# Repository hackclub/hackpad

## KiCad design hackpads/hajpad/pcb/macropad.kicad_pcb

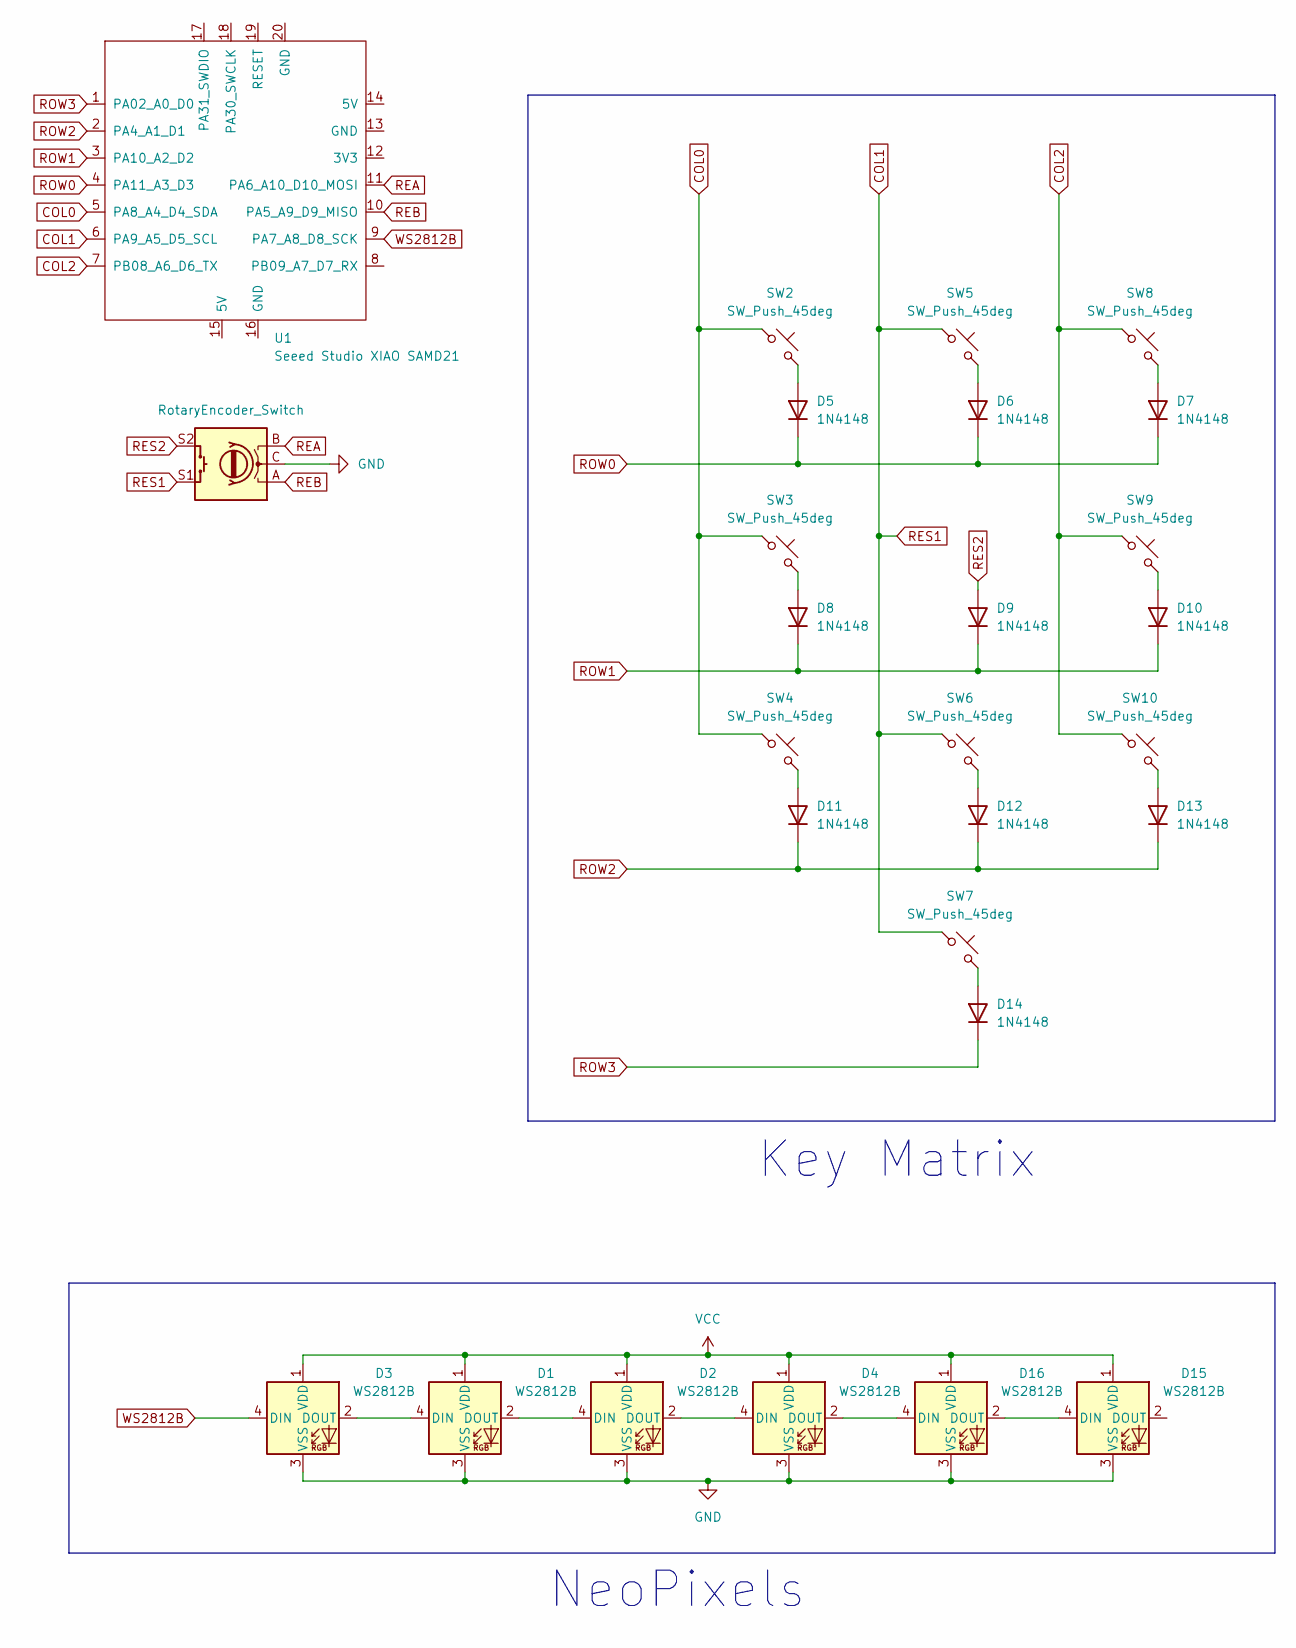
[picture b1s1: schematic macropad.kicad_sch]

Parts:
D1, D2, D3, D4, D15, D16: WS2812B; LED_WS2812B_PLCC4_5.0x5.0mm_P3.2mm
D5, D6, D7, D8, D9, D10, D11, D12, D13, D14: 1N4148; D_DO-35_SOD27_P7.62mm_Horizontal
SW1: RotaryEncoder_Switch; RotaryEncoder_Alps_EC11E-Switch_Vertical_H20mm_CircularMoun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
SW2, SW3, SW4, SW5, SW6, SW8, SW9, SW10: SW_Push_45deg; SW_Cherry_MX_PCB_1.00u
SW7: SW_Push_45deg; SW_Cherry_MX_PCB_3.00u_90deg
U1: Seeed Studio XIAO SAMD21; XIAO-Generic-Hybrid-14P-2.54-21X17.8MM0-alternate

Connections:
COL0: SW2.1, SW3.1, SW4.1, U1.5 (PA8_A4_D4_SDA)
COL1: SW1.S1, SW5.1, SW6.1, SW7.1, U1.6 (PA9_A5_D5_SCL)
COL2: SW8.1, SW9.1, SW10.1, U1.7 (PB08_A6_D6_TX)
GND: D1.3 (VSS), D2.3 (VSS), D3.3 (VSS), D4.3 (VSS), D15.3 (VSS), D16.3 (VSS), SW1.C
unnamed: D1.4 (DIN), D3.2 (DOUT)
unnamed: D1.2 (DOUT), D2.4 (DIN)
unnamed: D2.2 (DOUT), D4.4 (DIN)
unnamed: D5.2 (A), SW2.2
unnamed: D6.2 (A), SW5.2
unnamed: D7.2 (A), SW8.2
unnamed: D8.2 (A), SW3.2
unnamed: D10.2 (A), SW9.2
unnamed: D11.2 (A), SW4.2
unnamed: D12.2 (A), SW6.2
unnamed: D13.2 (A), SW10.2
unnamed: D14.2 (A), SW7.2
unnamed: D15.4 (DIN), D16.2 (DOUT)
unnamed: D4.2 (DOUT), D16.4 (DIN)
REA: SW1.B, U1.11 (PA6_A10_D10_MOSI)
REB: SW1.A, U1.10 (PA5_A9_D9_MISO)
RES2: D9.2 (A), SW1.S2
ROW0: D5.1 (K), D6.1 (K), D7.1 (K), U1.4 (PA11_A3_D3)
ROW1: D8.1 (K), D9.1 (K), D10.1 (K), U1.3 (PA10_A2_D2)
ROW2: D11.1 (K), D12.1 (K), D13.1 (K), U1.2 (PA4_A1_D1)
ROW3: D14.1 (K), U1.1 (PA02_A0_D0)
VCC: D1.1 (VDD), D2.1 (VDD), D3.1 (VDD), D4.1 (VDD), D15.1 (VDD), D16.1 (VDD)
WS2812B: D3.4 (DIN), U1.9 (PA7_A8_D8_SCK)

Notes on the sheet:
NeoPixels
Key Matrix

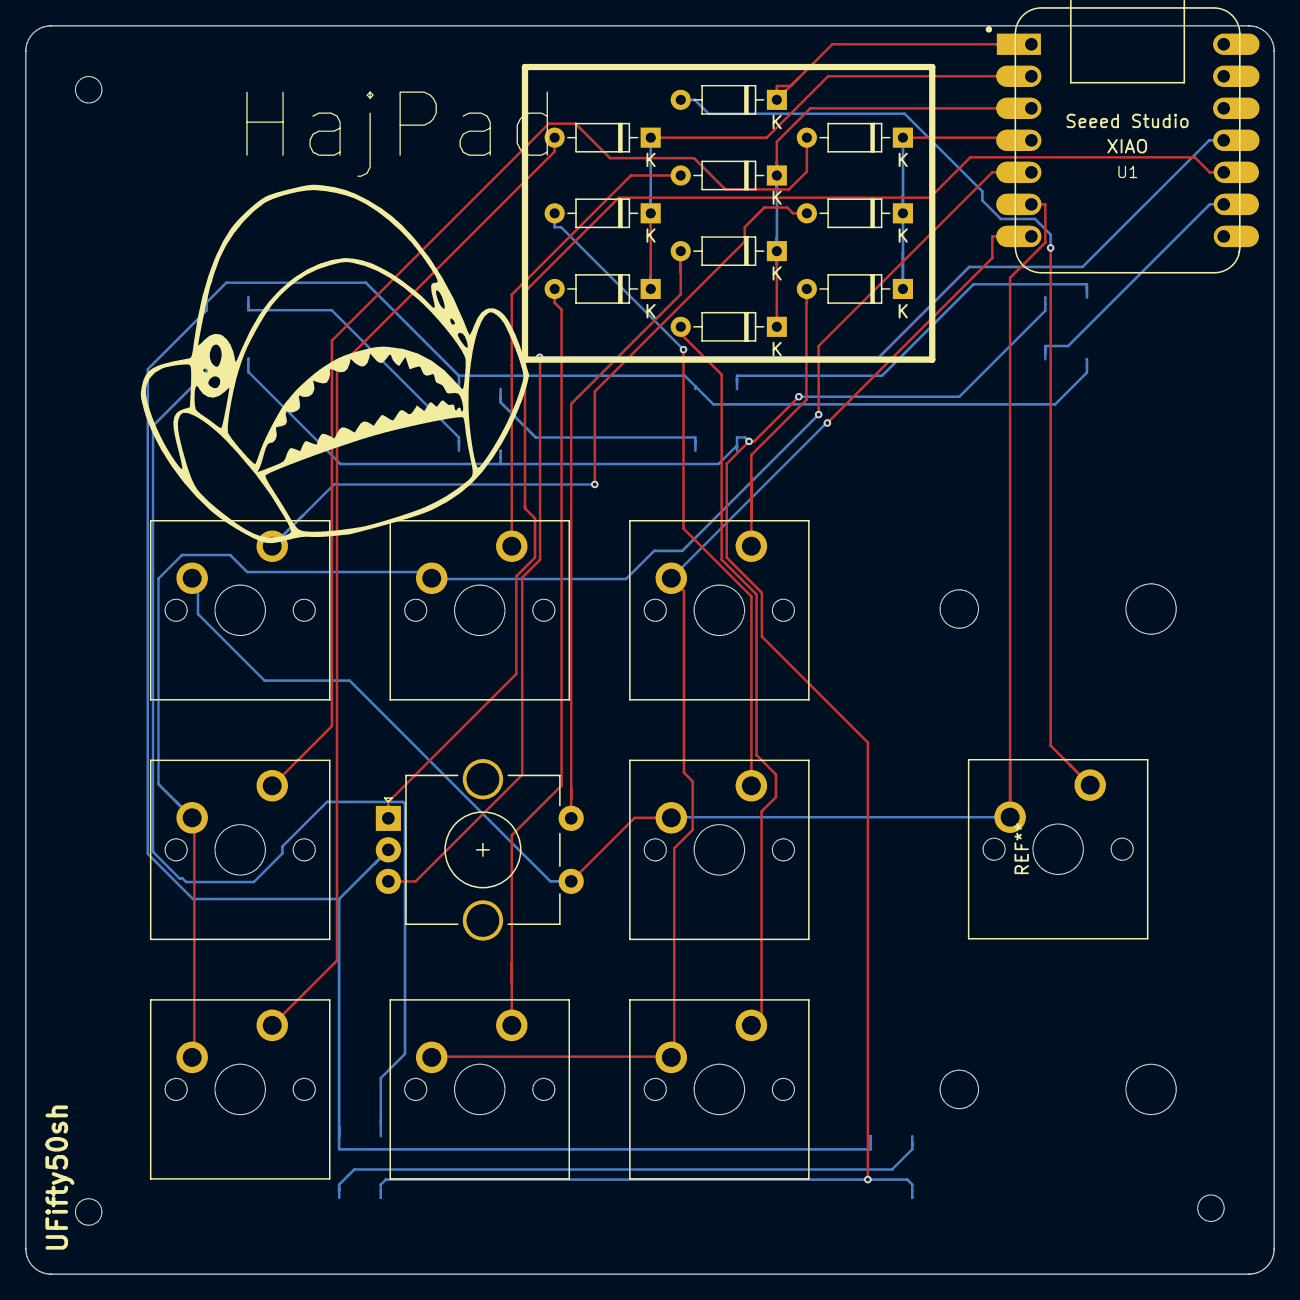
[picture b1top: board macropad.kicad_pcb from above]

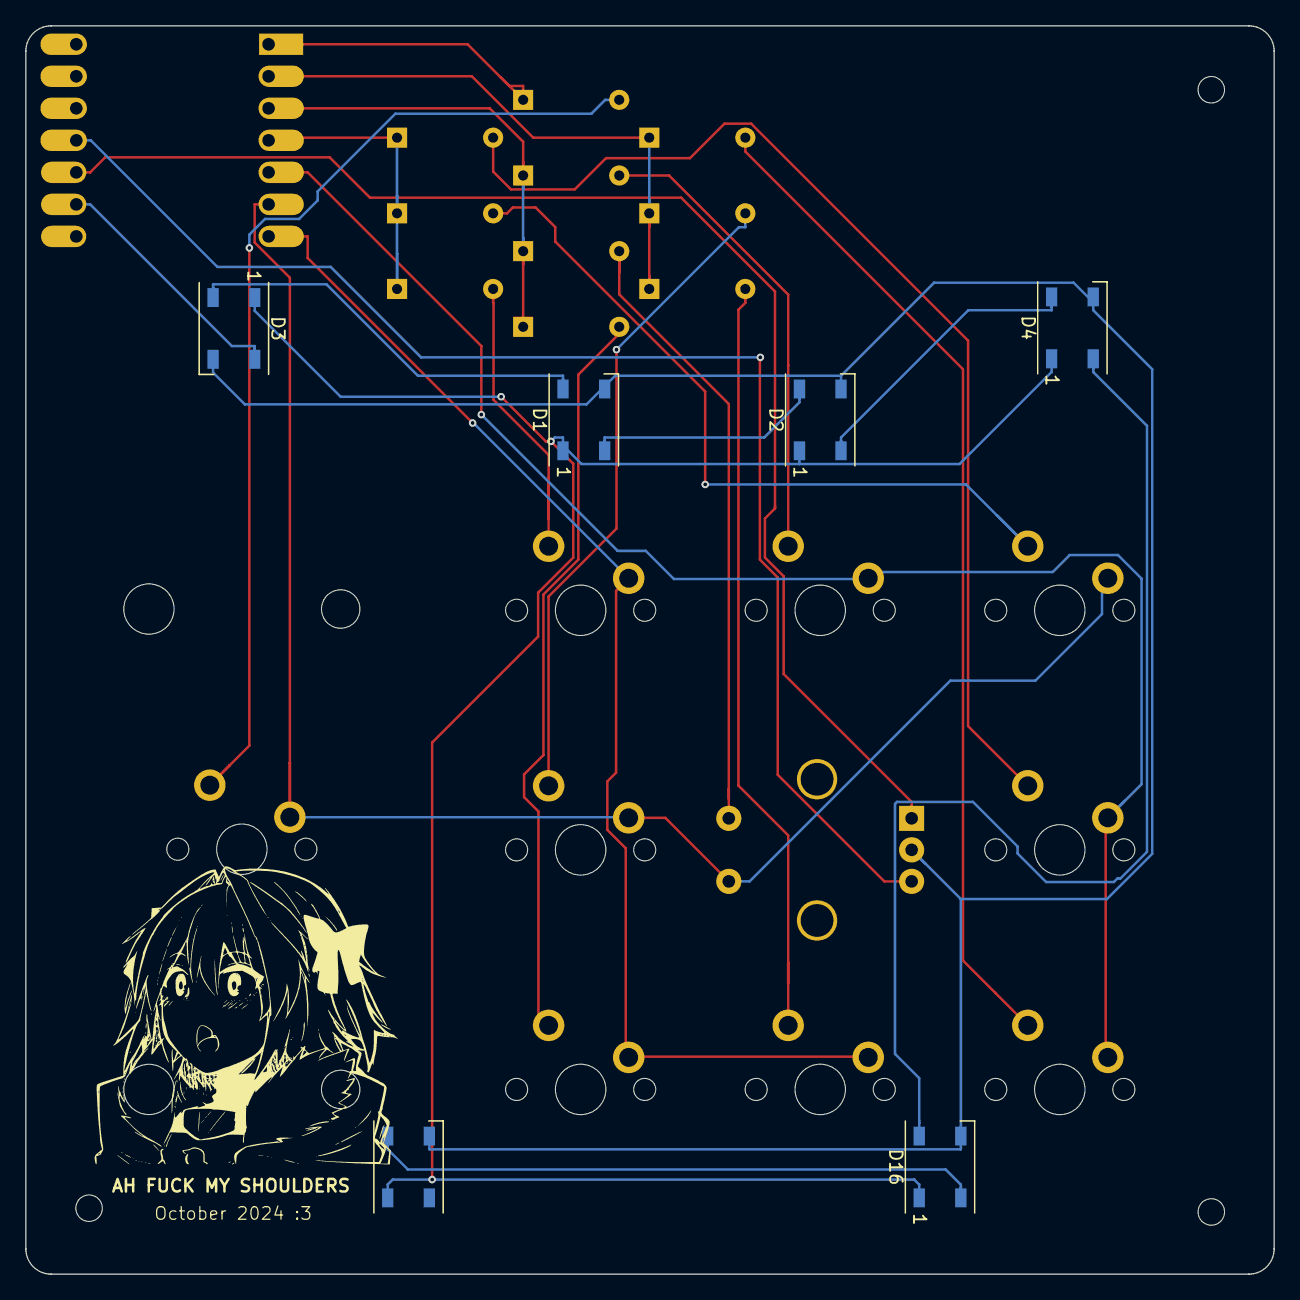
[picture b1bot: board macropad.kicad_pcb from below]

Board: 2 copper layers, 99.0 x 99.0 mm, 27 parts (6 on the bottom side), 27 nets.

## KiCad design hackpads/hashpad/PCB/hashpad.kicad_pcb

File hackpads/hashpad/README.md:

# Hash-AK's Hackpad (HashPad)

This is my macropad, made for the (awesome!) Hackpad V2 program of Hackclub (https://hackpad.hackclub.com)

I will use this hackpad for (eventually) Hyprland control (like workspace switching) or as a mini protable keyboard (TBD)

What I found particuliary difficult was the case design, I couldn't use Fusion and FreeCAD was hard to use, even with the tutorial (Cyao in the slack helped me alot for that).

# Features

- OLED Display
- Reverse-mounted LEDs to make a full backlighting
- Rotary Encoder to control some stuff
- Matrix with diodes to prevent ghosting

BOM :

- 1x trought-hole SEEED XIAO RP2040
- 9x MX-Style switches (preferably transluent one)
- 9x SK8612-e MINI led (for reverse mounting)
- 1x Rotary Encoder EC11
- 1x SD1306 0.96" OLED display
- 9x Through-hole 1N4148 Diodes
- 4x M3x16mm screws
- 4x M3 hex nuts

# Images

_Scheatics of the macropad_

_PCB of the macropad_

_Front of the board (3D Model)_

_Back of the board (3D Model, the SK8612 is missing in the images, there's only a cutout/pads)_

_Full image of the case with the PCB._

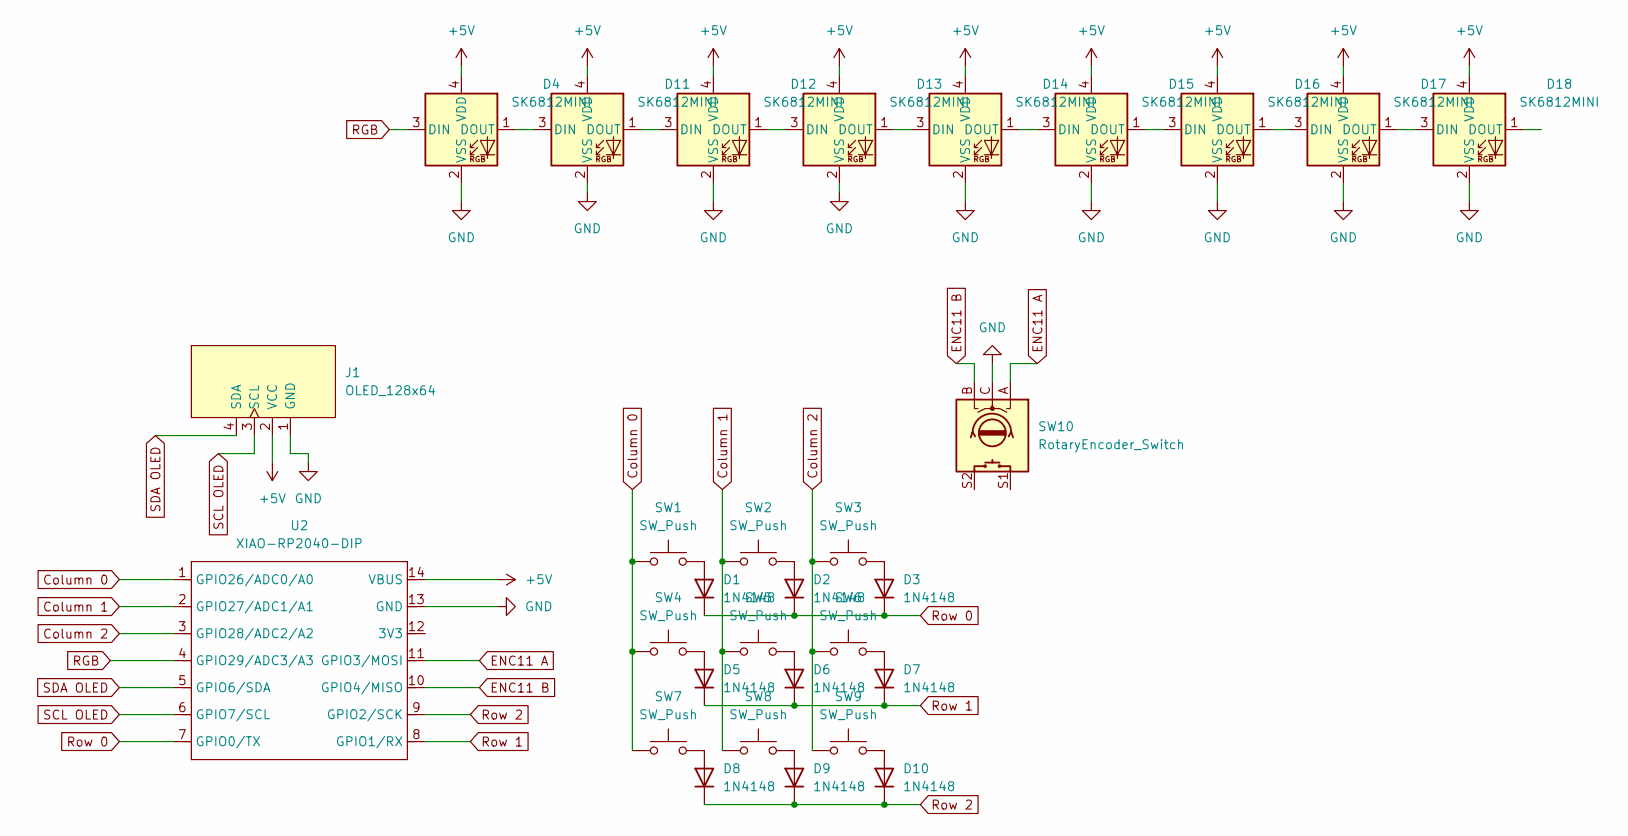
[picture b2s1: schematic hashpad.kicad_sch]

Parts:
D1, D2, D3, D5, D6, D7, D8, D9, D10: 1N4148; D_DO-35_SOD27_P7.62mm_Horizontal
D4, D11, D12, D13, D14, D15, D16, D17, D18: SK6812MINI; SK6812MINI-E
J1: OLED_128x64
SW1, SW2, SW3, SW4, SW5, SW6, SW7, SW8, SW9: SW_Push; MX_PCB_1.00u
SW10: RotaryEncoder_Switch; Encoder_EC11_MX
U2: XIAO-RP2040-DIP; Seeed_XIAO_RP2040

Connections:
+5V: D4.4 (VDD), D11.4 (VDD), D12.4 (VDD), D13.4 (VDD), D14.4 (VDD), D15.4 (VDD), D16.4 (VDD), D17.4 (VDD), D18.4 (VDD), J1.2 (VCC), U2.14 (VBUS)
Column 0: SW1.1, SW4.1, SW7.1, U2.1 (GPIO26/ADC0/A0)
Column 1: SW2.1, SW5.1, SW8.1, U2.2 (GPIO27/ADC1/A1)
Column 2: SW3.1, SW6.1, SW9.1, U2.3 (GPIO28/ADC2/A2)
ENC11 A: SW10.A, U2.11 (GPIO3/MOSI)
ENC11 B: SW10.B, U2.10 (GPIO4/MISO)
GND: D4.2 (VSS), D11.2 (VSS), D12.2 (VSS), D13.2 (VSS), D14.2 (VSS), D15.2 (VSS), D16.2 (VSS), D17.2 (VSS), D18.2 (VSS), J1.1 (GND), SW10.C, U2.13 (GND)
unnamed: D1.2 (A), SW1.2
unnamed: D2.2 (A), SW2.2
unnamed: D3.2 (A), SW3.2
unnamed: D5.2 (A), SW4.2
unnamed: D6.2 (A), SW5.2
unnamed: D7.2 (A), SW6.2
unnamed: D8.2 (A), SW7.2
unnamed: D9.2 (A), SW8.2
unnamed: D10.2 (A), SW9.2
unnamed: D4.1 (DOUT), D11.3 (DIN)
unnamed: D11.1 (DOUT), D12.3 (DIN)
unnamed: D12.1 (DOUT), D13.3 (DIN)
unnamed: D13.1 (DOUT), D14.3 (DIN)
unnamed: D14.1 (DOUT), D15.3 (DIN)
unnamed: D15.1 (DOUT), D16.3 (DIN)
unnamed: D16.1 (DOUT), D17.3 (DIN)
unnamed: D17.1 (DOUT), D18.3 (DIN)
RGB: D4.3 (DIN), U2.4 (GPIO29/ADC3/A3)
Row 0: D1.1 (K), D2.1 (K), D3.1 (K), U2.7 (GPIO0/TX)
Row 1: D5.1 (K), D6.1 (K), D7.1 (K), U2.8 (GPIO1/RX)
Row 2: D8.1 (K), D9.1 (K), D10.1 (K), U2.9 (GPIO2/SCK)
SCL OLED: J1.3 (SCL), U2.6 (GPIO7/SCL)
SDA OLED: J1.4 (SDA), U2.5 (GPIO6/SDA)

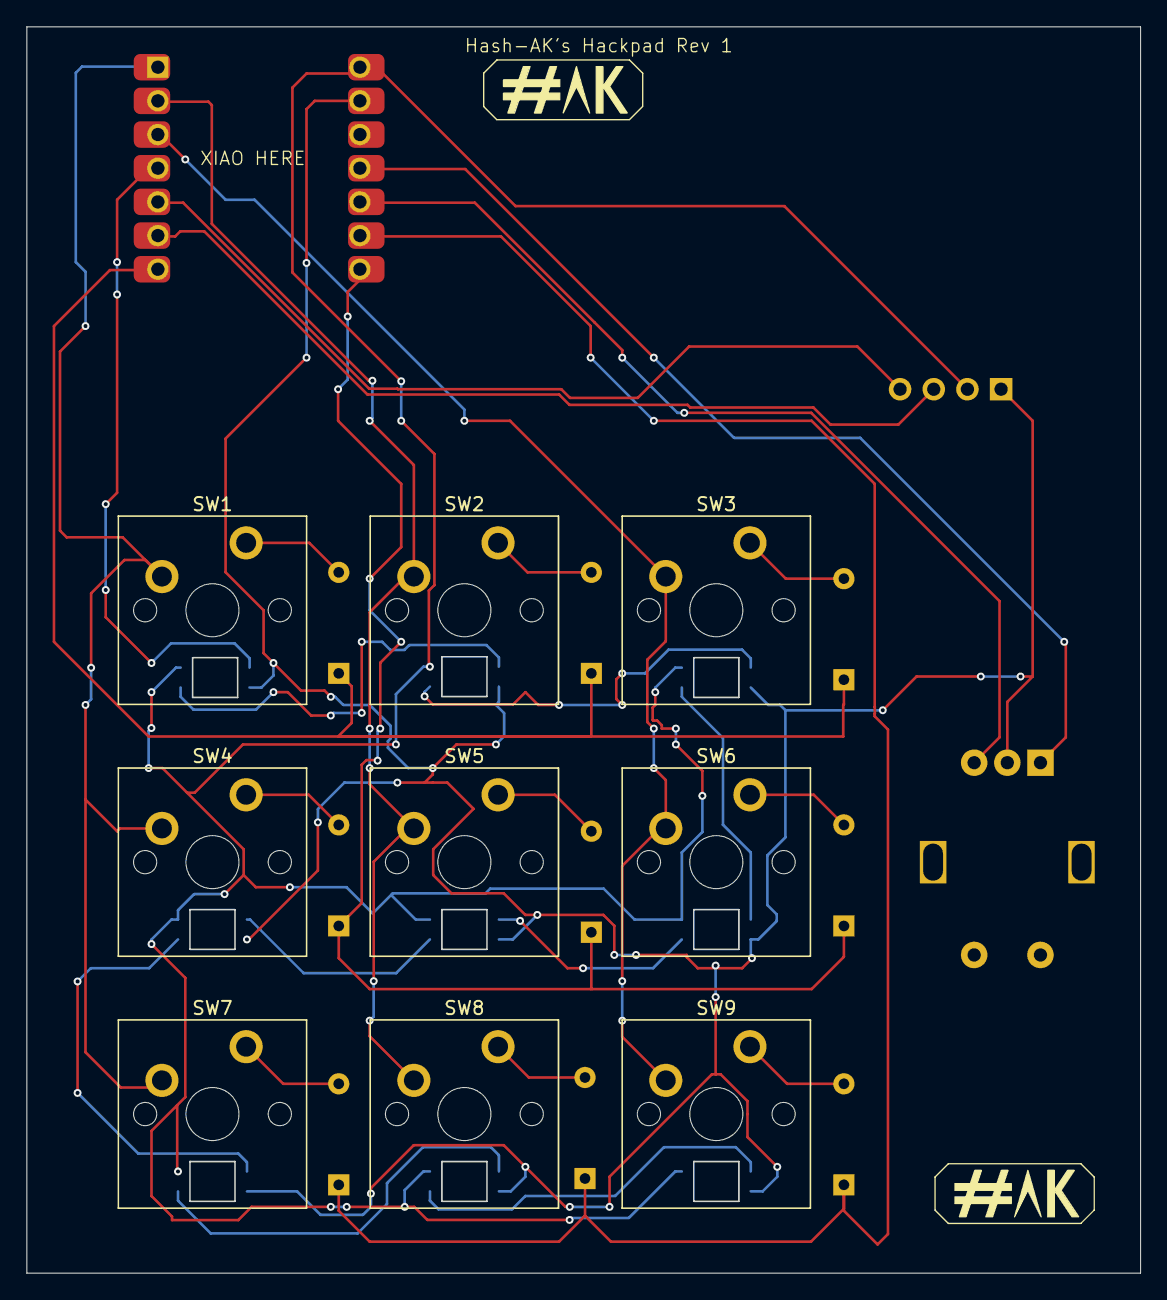
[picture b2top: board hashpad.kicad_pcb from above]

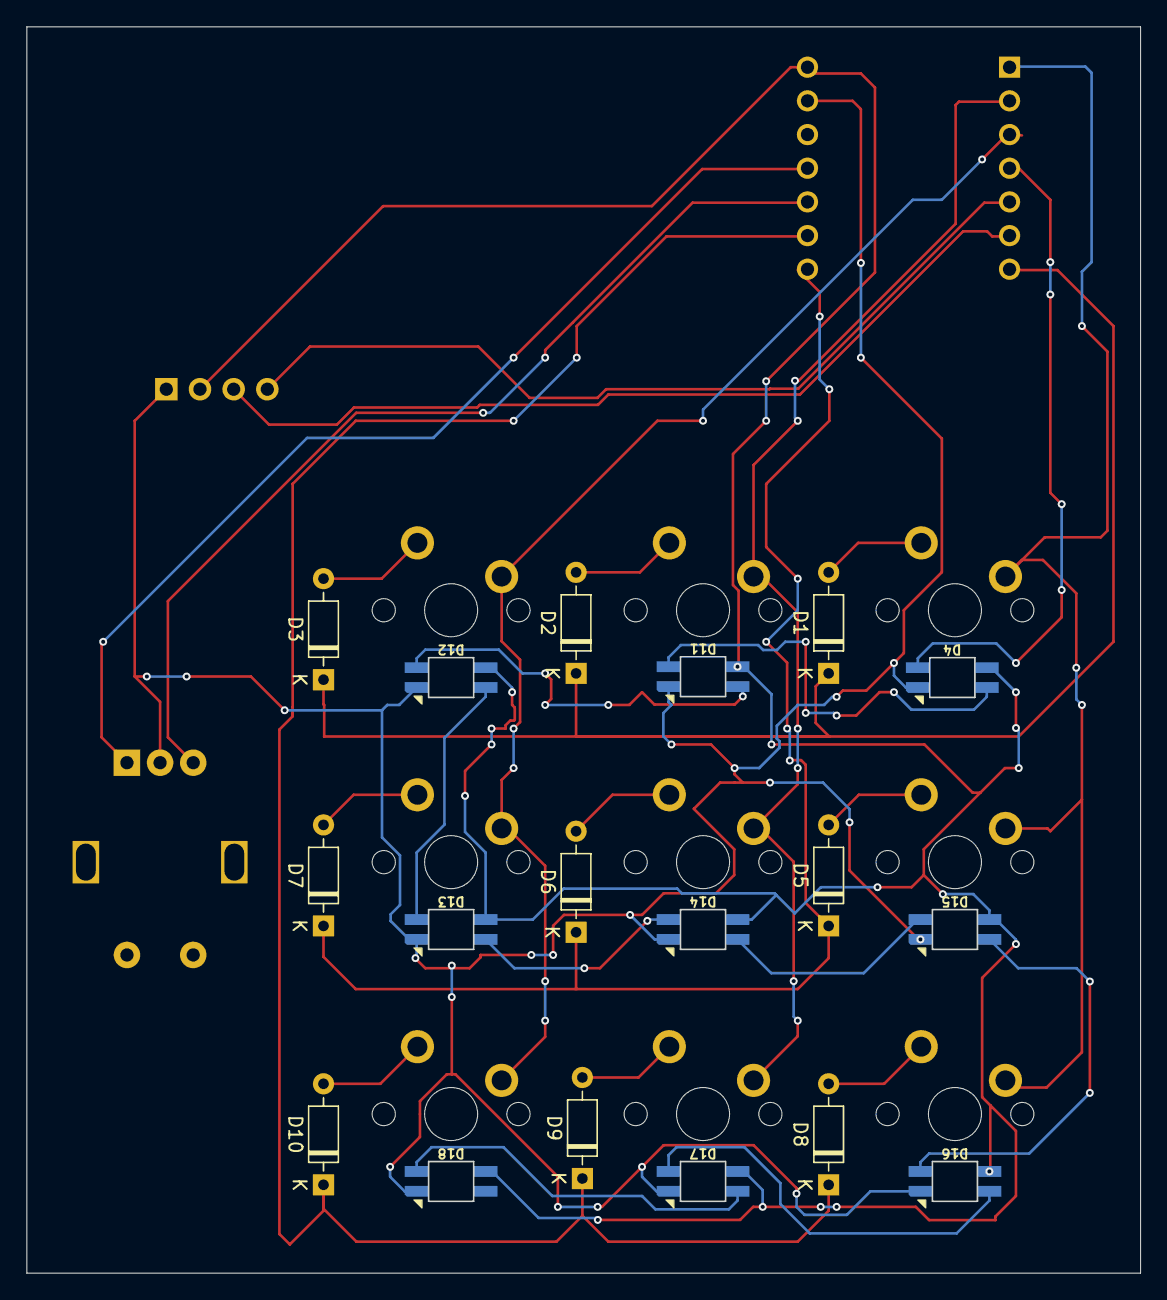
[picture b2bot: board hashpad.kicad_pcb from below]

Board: 2 copper layers, 84.0 x 94.0 mm, 30 parts (18 on the bottom side), 30 nets.

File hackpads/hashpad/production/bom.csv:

Designator,Footprint,Quantity,Value,LCSC Part #
"D1, D10, D2, D3, D5, D6, D7, D8, D9",D_DO-35_SOD27_P7.62mm_Horizontal,9,1N4148,
"D11, D12, D13, D14, D15, D16, D17, D18, D4",SK6812MINI-E,9,SK6812MINI,
J1,OLED_128x64,1,OLED_128x64,
"SW1, SW2, SW3, SW4, SW5, SW6, SW7, SW8, SW9",MX_PCB_1.00u,9,SW_Push,
SW10,Encoder_EC11_MX,1,RotaryEncoder_Switch,
U2,Seeed_XIAO_RP2040,1,XIAO-RP2040-DIP,

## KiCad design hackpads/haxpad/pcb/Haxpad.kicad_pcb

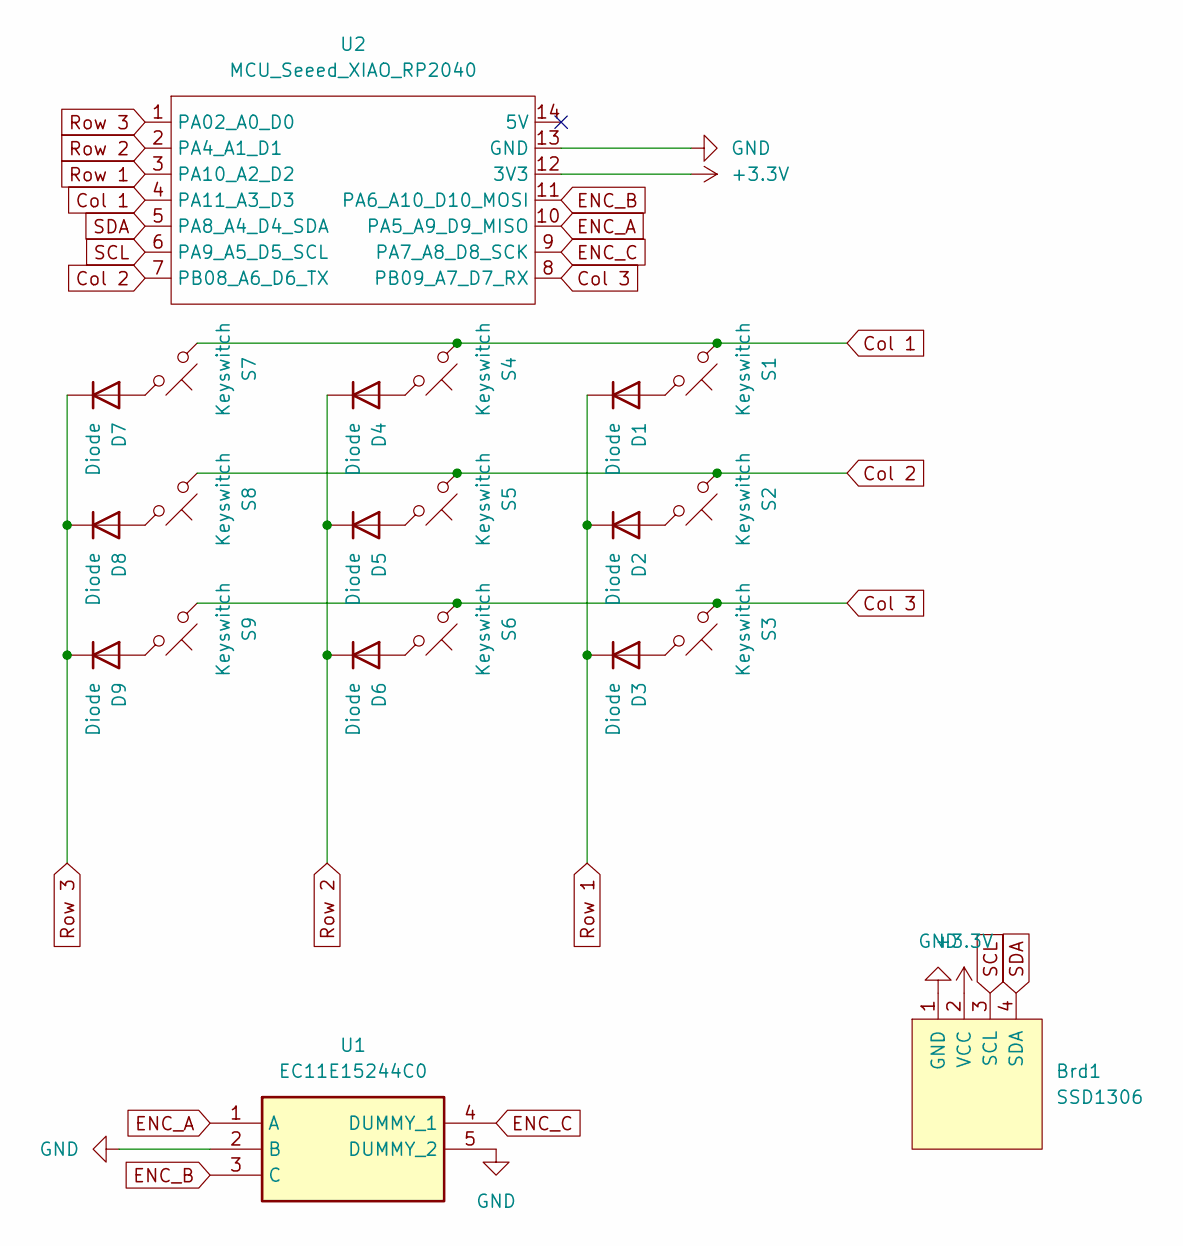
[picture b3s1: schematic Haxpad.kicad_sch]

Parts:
Brd1: SSD1306; 128x64OLED
D1, D2, D3, D4, D5, D6, D7, D8, D9: Diode; Diode_DO-35
S1, S2, S3, S4, S5, S6, S7, S8, S9: Keyswitch; MX-Hotswap-1U
U1: EC11E15244C0; EC11B202440M; Manufacturer_Part_Number EC11E15244C0
U2: MCU_Seeed_XIAO_RP2040; Seeed_XIAO_RP2040

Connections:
+3.3V: Brd1.2 (VCC), U2.12 (3V3)
Col 1: S1.1, S4.1, S7.1, U2.4 (PA11_A3_D3)
Col 2: S2.1, S5.1, S8.1, U2.7 (PB08_A6_D6_TX)
Col 3: S3.1, S6.1, S9.1, U2.8 (PB09_A7_D7_RX)
ENC_A: U1.1 (A), U2.10 (PA5_A9_D9_MISO)
ENC_B: U1.3 (C), U2.11 (PA6_A10_D10_MOSI)
ENC_C: U1.4 (DUMMY_1), U2.9 (PA7_A8_D8_SCK)
GND: Brd1.1 (GND), U1.2 (B), U1.5 (DUMMY_2), U2.13 (GND)
unnamed: D1.2 (A), S1.2
unnamed: D2.2 (A), S2.2
unnamed: D3.2 (A), S3.2
unnamed: D4.2 (A), S4.2
unnamed: D5.2 (A), S5.2
unnamed: D6.2 (A), S6.2
unnamed: D7.2 (A), S7.2
unnamed: D8.2 (A), S8.2
unnamed: D9.2 (A), S9.2
Row 1: D1.1 (K), D2.1 (K), D3.1 (K), U2.3 (PA10_A2_D2)
Row 2: D4.1 (K), D5.1 (K), D6.1 (K), U2.2 (PA4_A1_D1)
Row 3: D7.1 (K), D8.1 (K), D9.1 (K), U2.1 (PA02_A0_D0)
SCL: Brd1.3 (SCL), U2.6 (PA9_A5_D5_SCL)
SDA: Brd1.4 (SDA), U2.5 (PA8_A4_D4_SDA)

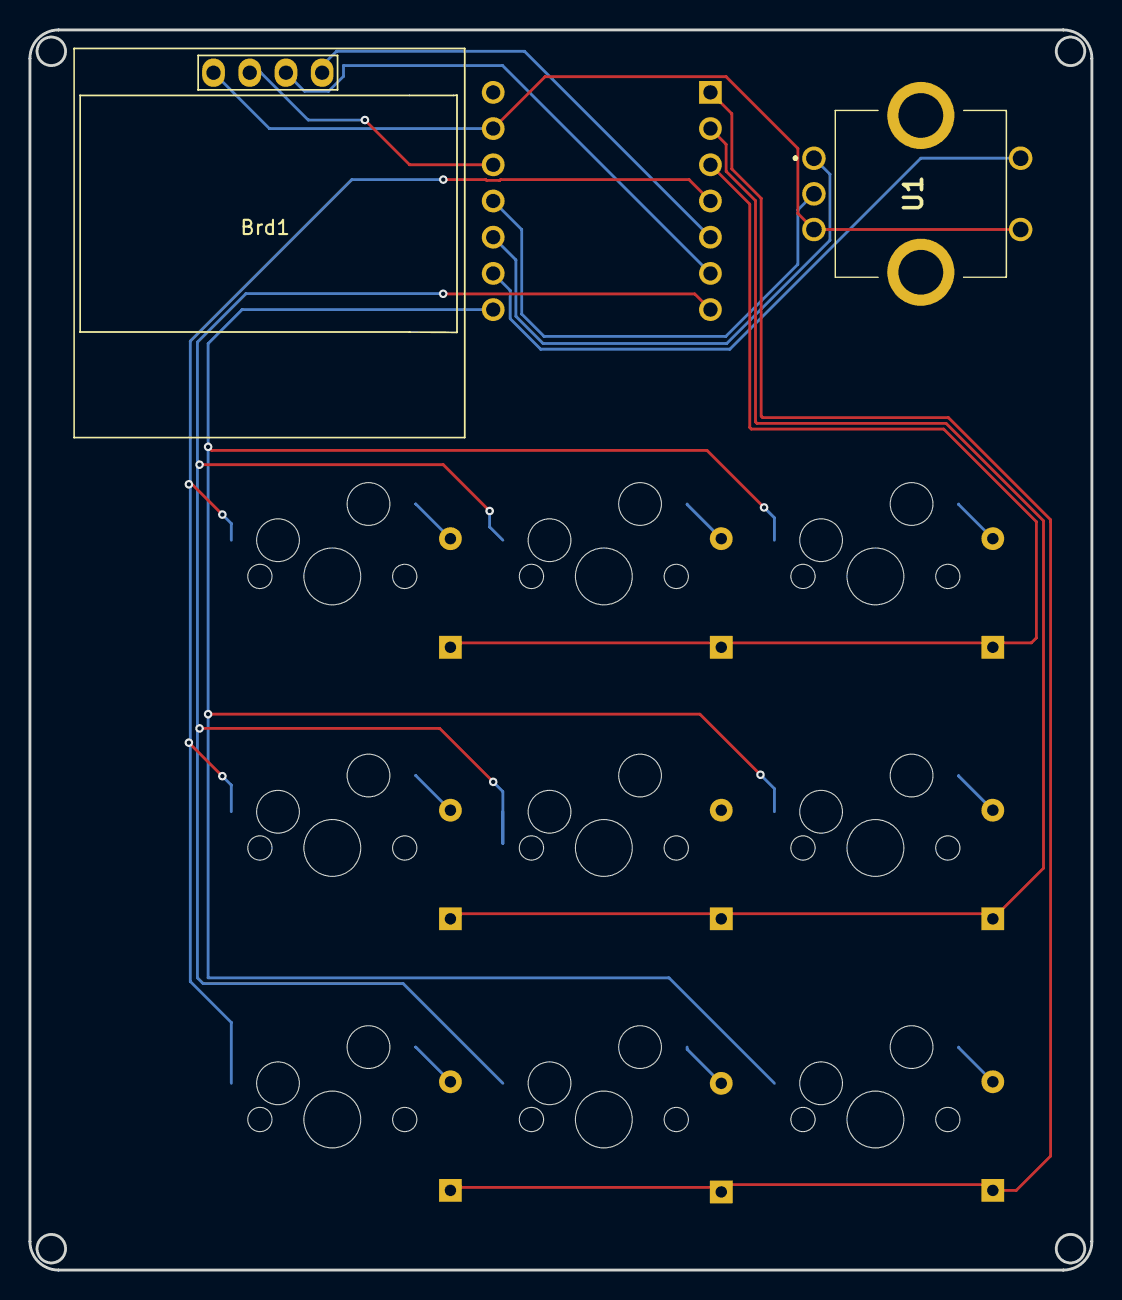
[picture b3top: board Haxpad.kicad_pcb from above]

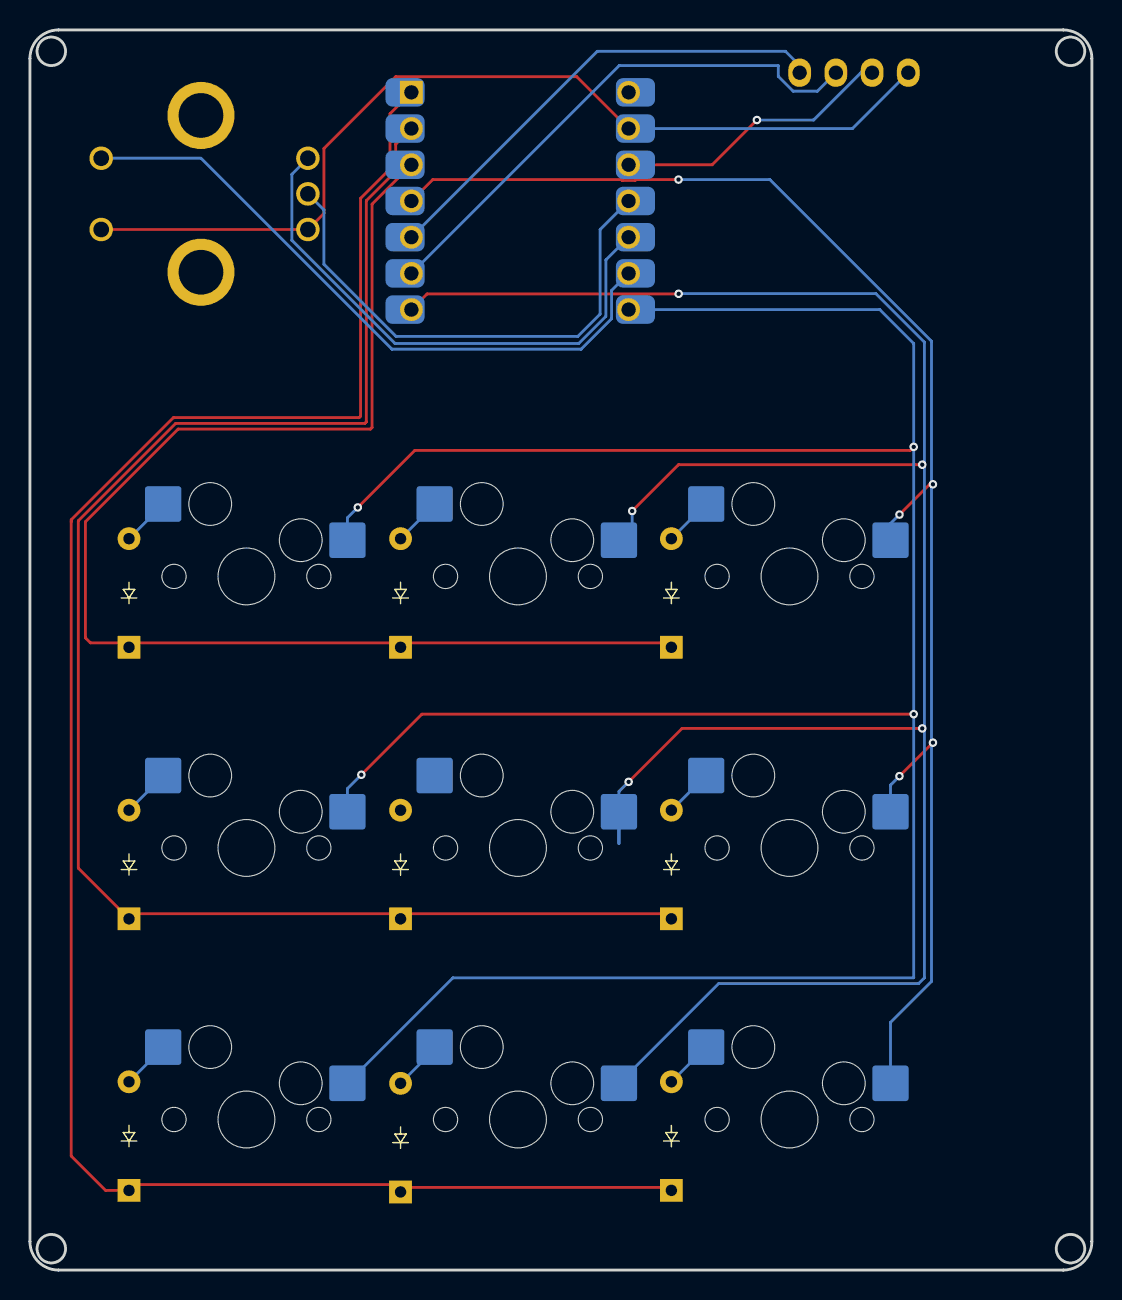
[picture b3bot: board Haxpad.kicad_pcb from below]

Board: 2 copper layers, 74.5 x 87.0 mm, 21 parts (19 on the bottom side), 22 nets.

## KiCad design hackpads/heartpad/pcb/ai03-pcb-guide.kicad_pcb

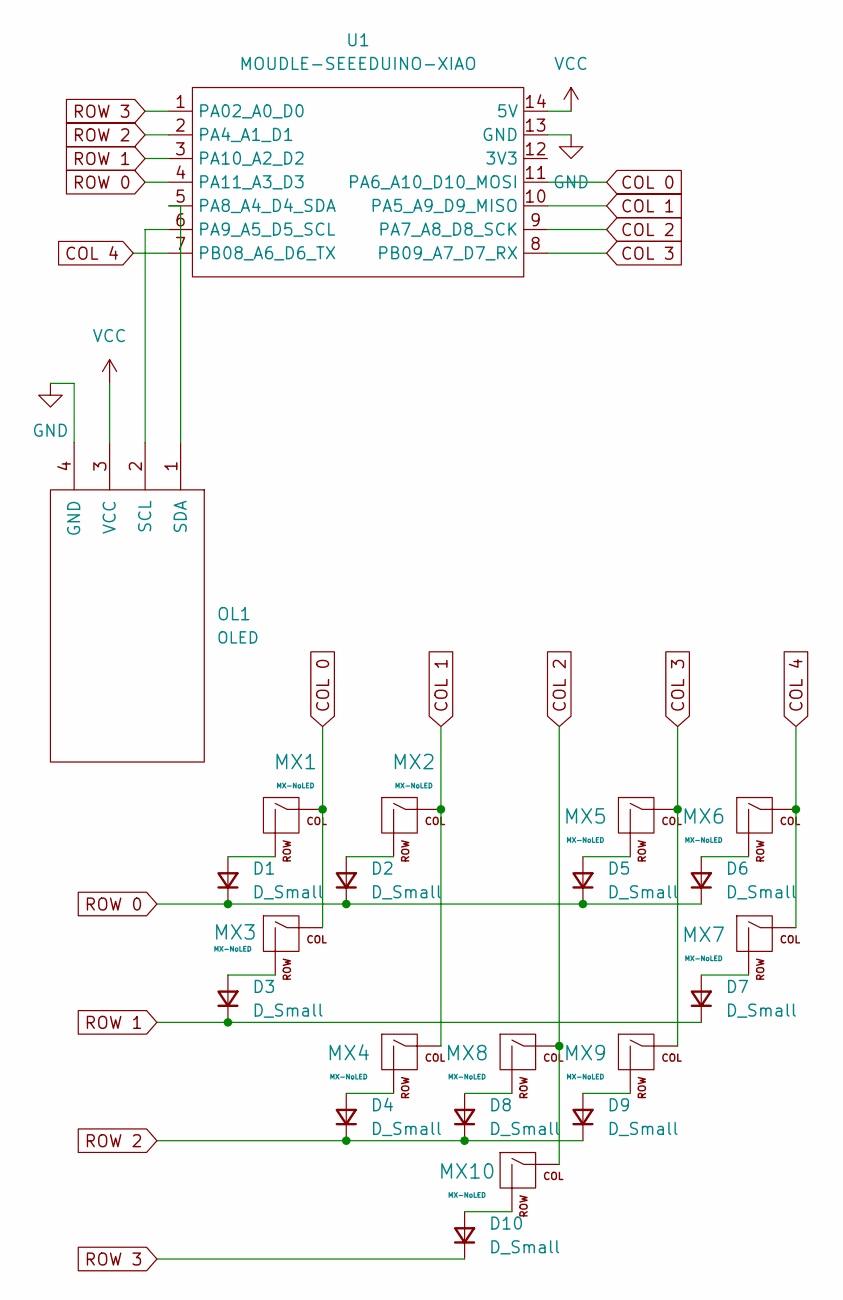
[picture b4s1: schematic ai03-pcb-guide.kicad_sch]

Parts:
D1, D2, D3, D4, D5, D6, D7, D8, D9, D10: D_Small; D_SOD-123
MX1, MX2, MX3, MX4, MX5, MX6, MX7, MX8, MX9, MX10: MX-NoLED; SW_Cherry_MX_1.00u_PCB
OL1: OLED
U1: MOUDLE-SEEEDUINO-XIAO; MOUDLE14P-2.54-21X17.8MM

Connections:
COL 0: MX1.1 (COL), MX3.1 (COL), U1.11 (PA6_A10_D10_MOSI)
COL 1: MX2.1 (COL), MX4.1 (COL), U1.10 (PA5_A9_D9_MISO)
COL 2: MX8.1 (COL), MX10.1 (COL), U1.9 (PA7_A8_D8_SCK)
COL 3: MX5.1 (COL), MX9.1 (COL), U1.8 (PB09_A7_D7_RX)
COL 4: MX6.1 (COL), MX7.1 (COL), U1.7 (PB08_A6_D6_TX)
GND: OL1.4 (GND), U1.13 (GND)
unnamed: D1.2 (A), MX1.2 (ROW)
unnamed: D2.2 (A), MX2.2 (ROW)
unnamed: D3.2 (A), MX3.2 (ROW)
unnamed: D4.2 (A), MX4.2 (ROW)
unnamed: D5.2 (A), MX5.2 (ROW)
unnamed: D6.2 (A), MX6.2 (ROW)
unnamed: D7.2 (A), MX7.2 (ROW)
unnamed: D8.2 (A), MX8.2 (ROW)
unnamed: D9.2 (A), MX9.2 (ROW)
unnamed: D10.2 (A), MX10.2 (ROW)
unnamed: OL1.2 (SCL), U1.6 (PA9_A5_D5_SCL)
unnamed: OL1.1 (SDA), U1.5 (PA8_A4_D4_SDA)
ROW 0: D1.1 (K), D2.1 (K), D5.1 (K), D6.1 (K), U1.4 (PA11_A3_D3)
ROW 1: D3.1 (K), D7.1 (K), U1.3 (PA10_A2_D2)
ROW 2: D4.1 (K), D8.1 (K), D9.1 (K), U1.2 (PA4_A1_D1)
ROW 3: D10.1 (K), U1.1 (PA02_A0_D0)
VCC: OL1.3 (VCC), U1.14 (5V)

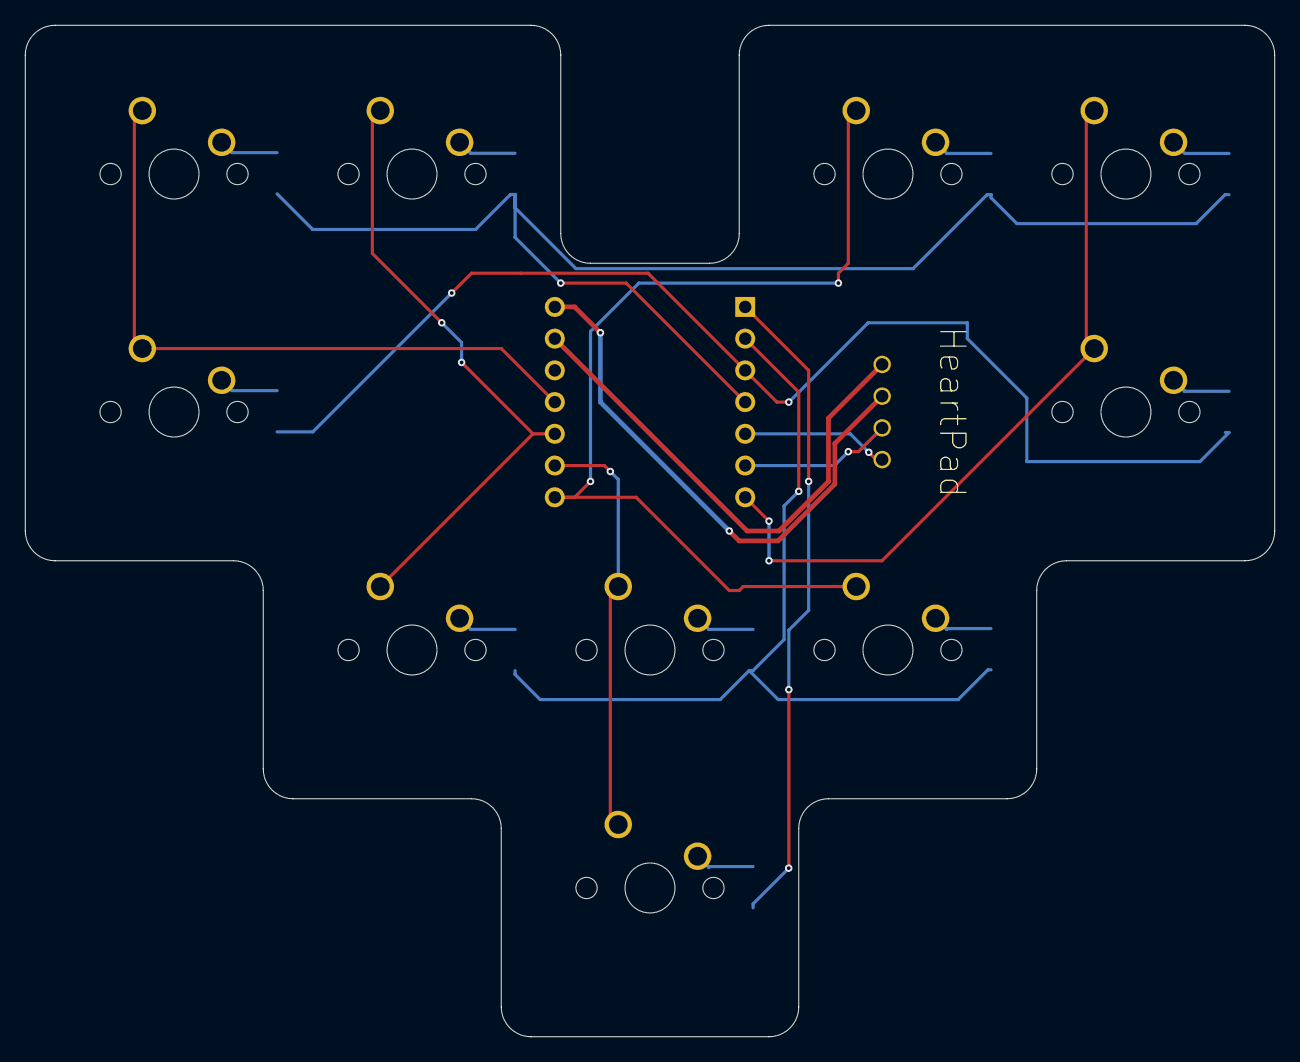
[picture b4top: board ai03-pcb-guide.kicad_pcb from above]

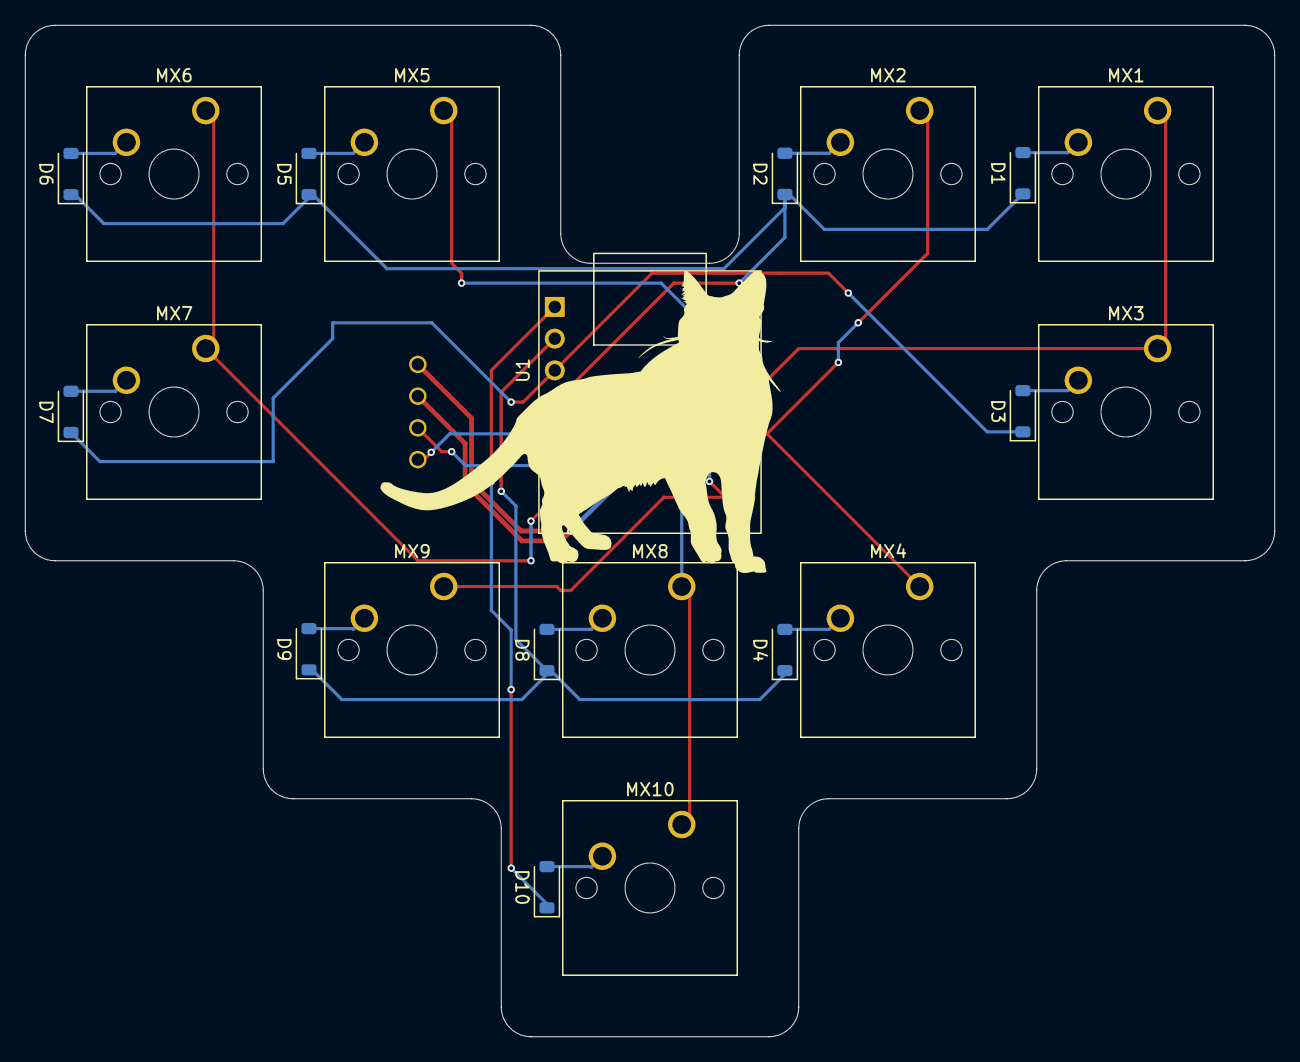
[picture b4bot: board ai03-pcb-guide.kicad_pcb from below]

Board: 2 copper layers, 100.0 x 81.0 mm, 22 parts (21 on the bottom side), 23 nets.
